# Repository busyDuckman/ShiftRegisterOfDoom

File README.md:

# ShiftRegisterOfDoom  
A TPIC6B595 breakout board (TTL), with related Arduino libraries.  
  
** This is not finished yet **

** Notes: **
  - This is my first KiCad project, I am trasitioning from eagleCad so right now I am probably doing things I will cringe at later.
  - I am building this for a trainset, so some design considerations reflect that.
  
** The Breakout board:  **  
  Created using [KiCad](http://kicad-pcb.org/)  
  Source in \TPIC6B595_power_sift_reg_breakout  
  Spec sheets and sources of information used:
    - http://www.ti.com/lit/ds/symlink/tpic6b595.pdf
	- http://www.ti.com/lit/ds/symlink/tpic6a596.pdf
	- http://forum.arduino.cc/index.php?topic=288359.0
	- https://www.snapeda.com/parts/TPIC6B595/Texas%20Instruments/view-part/
  
** The Arduino Code:  **  
  Once the electrical work is done.

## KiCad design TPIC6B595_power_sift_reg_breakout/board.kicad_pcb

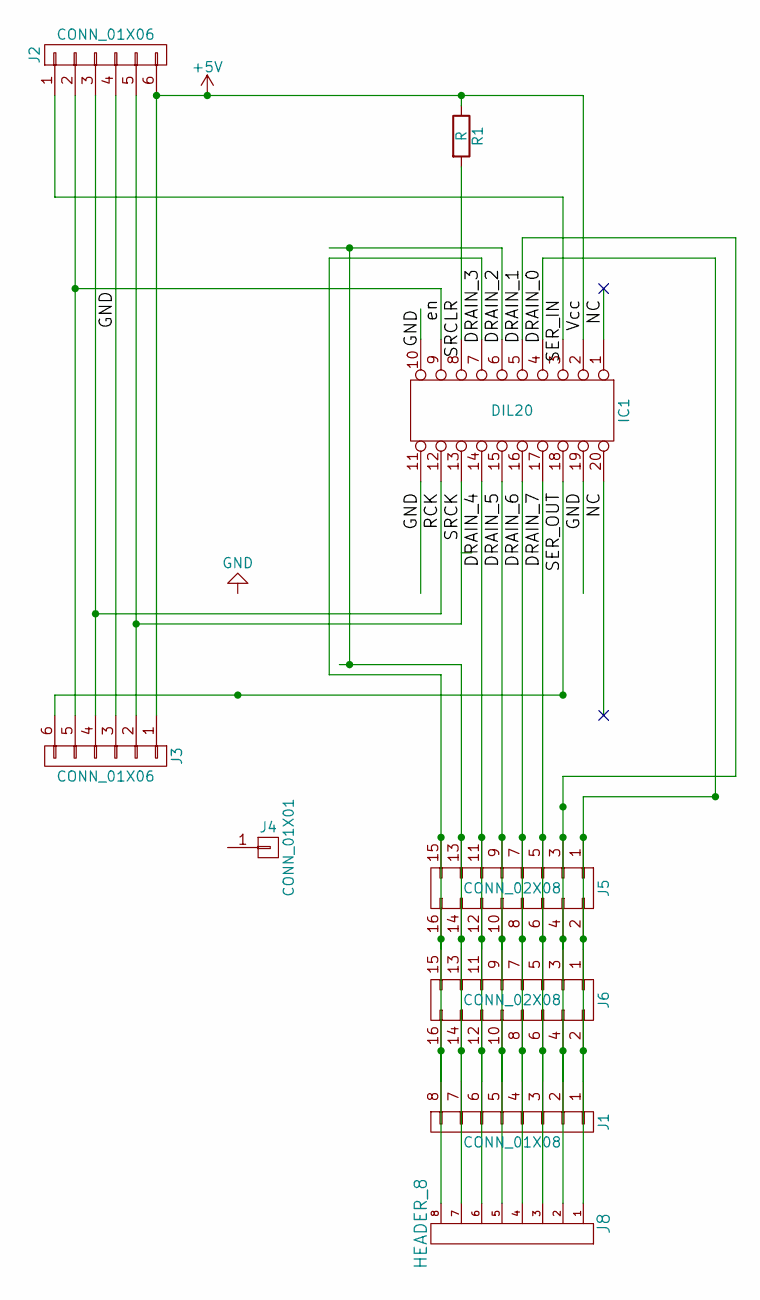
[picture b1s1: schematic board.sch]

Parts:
IC1: DIL20; DIP-20_W7.62mm_LongPads
J1: CONN_01X08; Pin_Header_Straight_1x08_Pitch2.54mm
J2, J3: CONN_01X06; Pin_Header_Angled_1x06_Pitch2.54mm
J4: CONN_01X01; Pin_Header_Straight_1x01_Pitch2.54mm
J5, J6: CONN_02X08; Pin_Header_Straight_2x08_Pitch2.54mm
J8: HEADER_8; PhoenixContact_MCV-GF_08x5.08mm_Vertical_ThreadedFlange
R1: R; R_Axial_DIN0204_L3.6mm_D1.6mm_P7.62mm_Horizontal

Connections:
+5V: IC1.2, J2.6, J3.1, R1.1
/DRAIN_0: IC1.4, J1.1, J5.1, J5.2, J6.1, J6.2, J8.1
/DRAIN_1: IC1.5, J1.2, J5.3, J5.4, J6.3, J6.4, J8.2
/DRAIN_2: IC1.6, J1.7, J5.13, J5.14, J6.13, J6.14, J8.7
/DRAIN_3: IC1.7, J1.8, J5.15, J5.16, J6.15, J6.16, J8.8
/DRAIN_4: IC1.14, J1.6, J5.11, J5.12, J6.11, J6.12, J8.6
/DRAIN_5: IC1.15, J1.5, J5.9, J5.10, J6.9, J6.10, J8.5
/DRAIN_6: IC1.16, J1.4, J5.7, J5.8, J6.7, J6.8, J8.4
/DRAIN_7: IC1.17, J1.3, J5.5, J5.6, J6.5, J6.6, J8.3
/NC: IC1.1, IC1.20
/RCK: IC1.12, J2.3, J3.4
/SER_IN: IC1.3, J2.1
/SER_OUT: IC1.18, J3.6
/SRCK: IC1.13, J2.5, J3.2
/SRCLR: IC1.8, R1.2
/en: IC1.9, J2.2, J3.5
GND: IC1.10, IC1.11, IC1.19, J2.4, J3.3

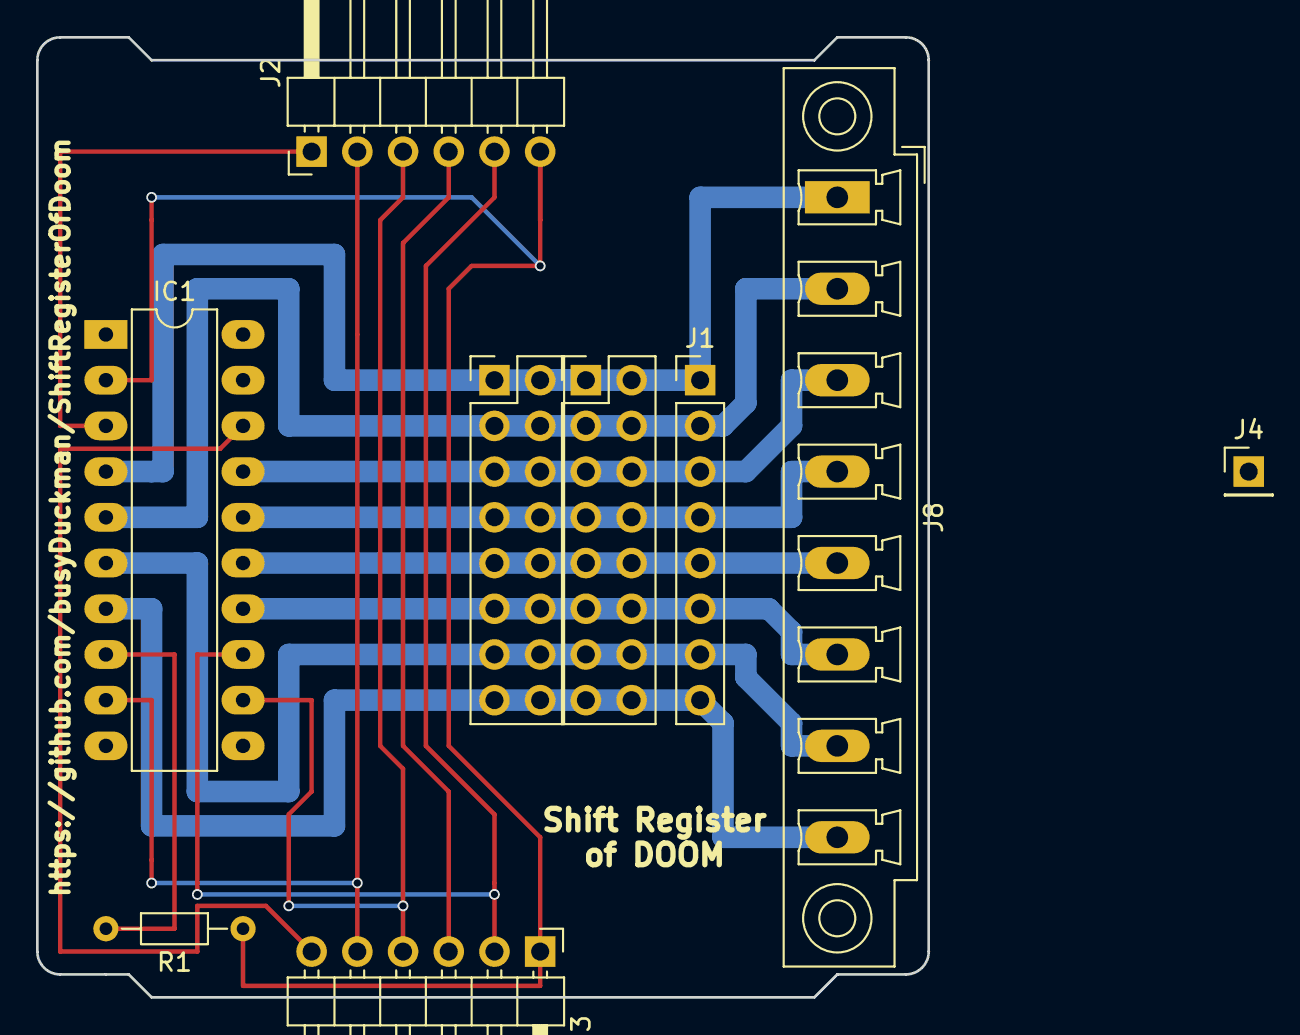
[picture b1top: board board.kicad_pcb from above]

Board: 2 copper layers, 49.5 x 53.3 mm, 9 parts (0 on the bottom side), 17 nets.

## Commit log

2017-09-08 First draft of board.
2017-09-18 misc work on PCB design
